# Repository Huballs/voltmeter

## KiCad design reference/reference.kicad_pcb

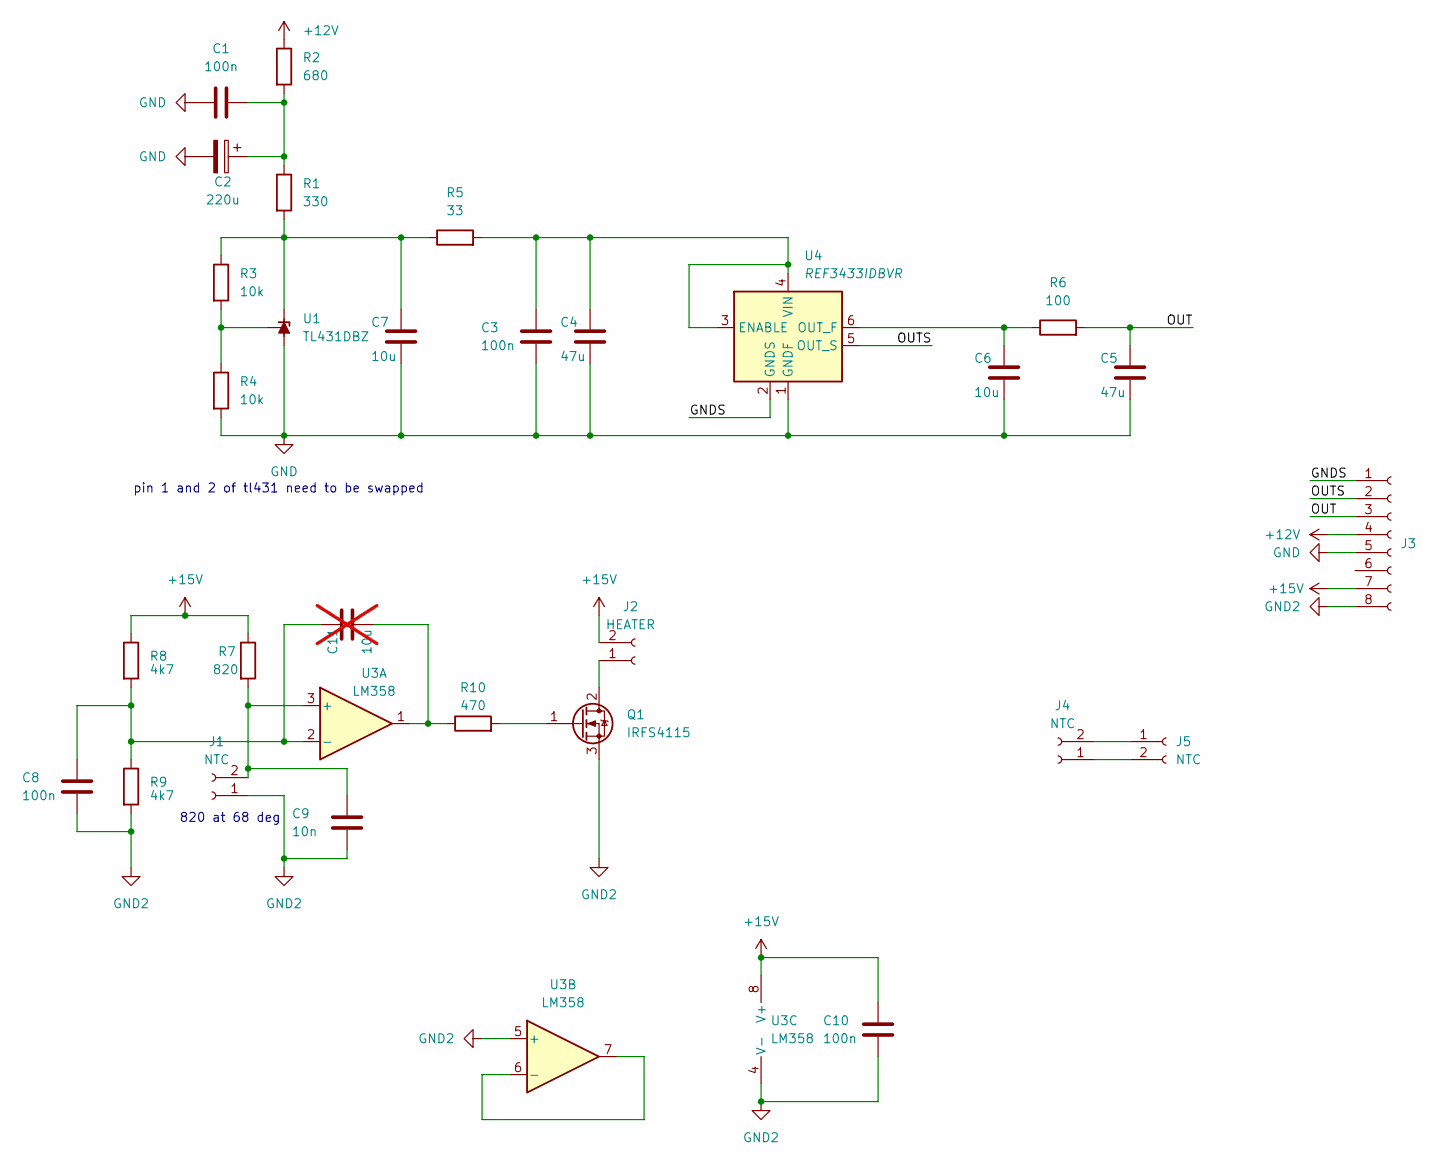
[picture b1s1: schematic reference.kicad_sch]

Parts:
C1, C3, C8, C10: 100n; C_0805_2012Metric_Pad1.18x1.45mm_HandSolder
C2: 220u; CP_EIA-7343-31_Kemet-D
C4, C5: 47u; C_0805_2012Metric_Pad1.18x1.45mm_HandSolder
C6, C7: 10u; C_0805_2012Metric_Pad1.18x1.45mm_HandSolder
C9: 10n; C_0805_2012Metric_Pad1.18x1.45mm_HandSolder
C11: 10u; C_0805_2012Metric_Pad1.18x1.45mm_HandSolder; not fitted
J1, J4, J5: NTC; PinHeader_1x02_P2.54mm_Vertical
J2: HEATER; PinHeader_1x02_P2.54mm_Vertical
J3: Conn_01x08_Socket; PinHeader_1x08_P2.54mm_Vertical
Q1: IRFS4115; TO-252-2
R1: 330; R_1206_3216Metric_Pad1.30x1.75mm_HandSolder
R2: 680; R_1206_3216Metric_Pad1.30x1.75mm_HandSolder
R3, R4: 10k; R_1206_3216Metric_Pad1.30x1.75mm_HandSolder
R5: 33; R_1206_3216Metric_Pad1.30x1.75mm_HandSolder
R6: 100; R_1206_3216Metric_Pad1.30x1.75mm_HandSolder
R7: 820; R_1206_3216Metric_Pad1.30x1.75mm_HandSolder
R8, R9: 4k7; R_1206_3216Metric_Pad1.30x1.75mm_HandSolder
R10: 470; R_1206_3216Metric_Pad1.30x1.75mm_HandSolder
U1: TL431DBZ; SOT-23
U3: LM358; SOIC-8_3.9x4.9mm_P1.27mm
U4: REF3433IDBVR; SOT-23-6

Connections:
+12V: J3.4, R2.1
+15V: C10.2, J2.2, J3.7, R7.1, R8.1, U3.8 (V+)
/GNDS: J3.1, U4.2 (GNDS)
/OUT: C5.2, J3.3, R6.2
/OUTS: J3.2, U4.5 (OUT_S)
GND: C1.1, C2.2, C3.1, C4.1, C5.1, C6.1, C7.1, J3.5, R4.2, U1.3 (A), U4.1 (GNDF)
GND2: C8.1, C9.1, C10.1, J1.1, J3.8, Q1.3 (S), R9.2, U3.4 (V-), U3.5 (+)
unnamed: C1.2, C2.1, R1.1, R2.2
unnamed: C11.1, R10.1, U3.1
unnamed: C9.2, J1.2, R7.2, U3.3 (+)
unnamed: J2.1, Q1.2 (D)
unnamed: J4.1, J5.2
unnamed: J4.2, J5.1
unnamed: Q1.1 (G), R10.2
unnamed: C7.2, R1.2, R3.1, R5.1, U1.1 (K)
unnamed: R3.2, R4.1, U1.2 (REF)
unnamed: C8.2, C11.2, R8.2, R9.1, U3.2 (-)
unnamed: U3.6 (-), U3.7
unnamed: C3.2, C4.2, R5.2, U4.3 (ENABLE), U4.4 (VIN)
unnamed: C6.2, R6.1, U4.6 (OUT_F)

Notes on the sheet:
pin 1 and 2 of tl431 need to be swapped
820 at 68 deg

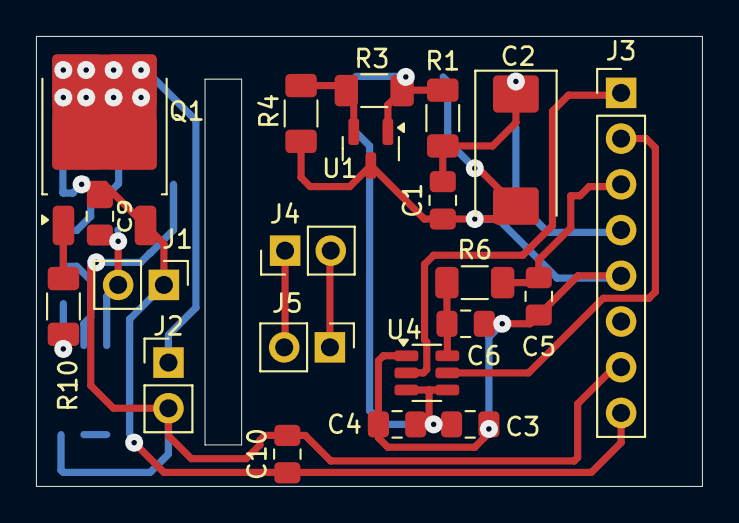
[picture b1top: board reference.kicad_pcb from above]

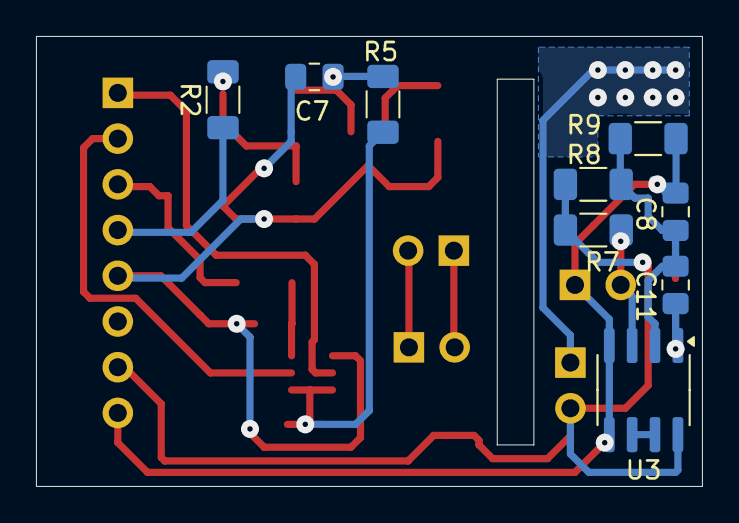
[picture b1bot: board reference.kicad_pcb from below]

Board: 2 copper layers, 37.0 x 25.0 mm, 30 parts (9 on the bottom side), 20 nets.

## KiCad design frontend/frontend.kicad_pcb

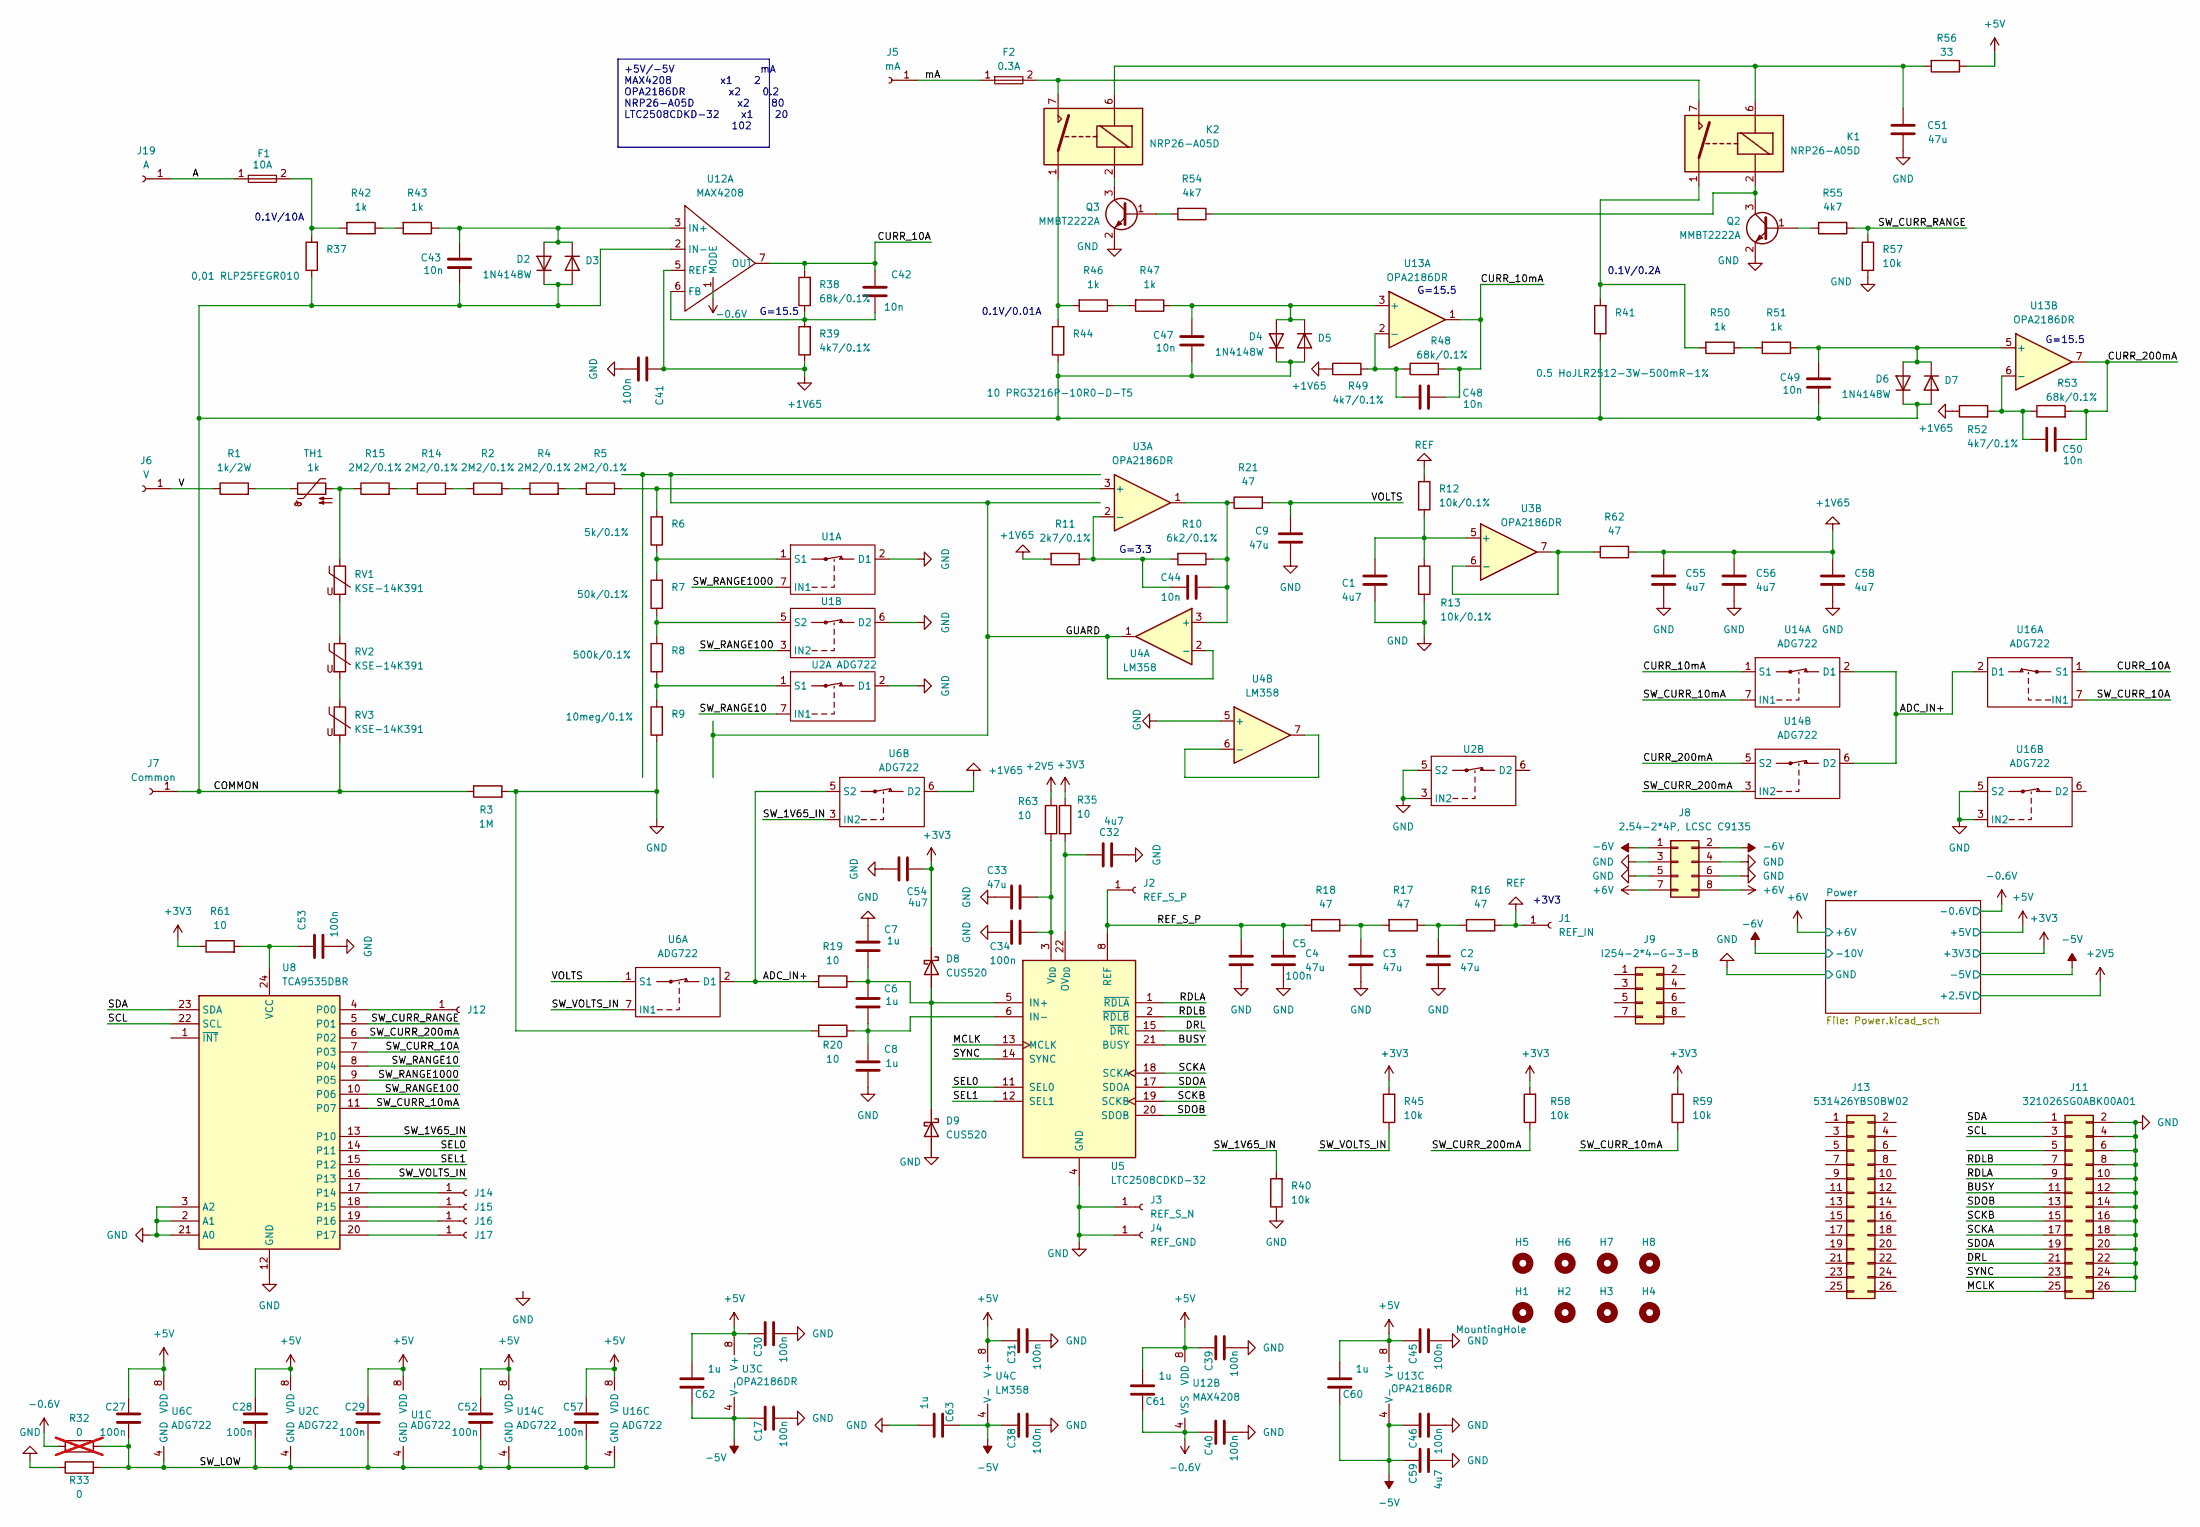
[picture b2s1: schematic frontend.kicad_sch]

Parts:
C1, C32, C54, C55, C56, C58, C59: 4u7; C_0805_2012Metric_Pad1.18x1.45mm_HandSolder
C2, C3, C4, C9, C33, C51: 47u; C_0805_2012Metric_Pad1.18x1.45mm_HandSolder
C5, C17, C27, C28, C29, C30, C31, C34, C38, C39, C40, C41, C45, C46, C52, C53, C57: 100n; C_0805_2012Metric_Pad1.18x1.45mm_HandSolder
C6, C7, C8, C60, C61, C62, C63: 1u; C_0805_2012Metric_Pad1.18x1.45mm_HandSolder
C42, C43, C44, C47, C48, C49, C50: 10n; C_0805_2012Metric_Pad1.18x1.45mm_HandSolder
D2, D3, D4, D5, D6, D7: 1N4148W; D_SOD-123
D8, D9: CUS520; D_SOD-323
F1: 10A; KLS5-266(FH-100)
F2: 0.3A; KLS5-266(FH-100)
H1, H2, H3, H4, H5, H6, H7, H8: MountingHole; MountingHole_3.2mm_M3
J1: REF_IN; PinHeader_1x01_P2.54mm_Vertical
J2: REF_S_P; PinHeader_1x01_P2.54mm_Vertical
J3: REF_S_N; PinHeader_1x01_P2.54mm_Vertical
J4: REF_GND; PinHeader_1x01_P2.54mm_Vertical
J5: mA; Conn-1-6x6-OD3mm
J6: V; Conn-1-6x6-OD3mm
J7: Common; Conn-1-6x6-OD3mm
J8: 2.54-2*4P, LCSC C9135; IDC-Header_2x04_P2.54mm_Vertical
J9: I254-2*4-G-3-B; IDC-Header_2x04_P2.54mm_Vertical
J11: 321026SG0ABK00A01; IDC-Header_2x13_P2.54mm_Vertical
J12, J14, J15, J16, J17: Conn_01x01_Socket; PinHeader_1x01_P2.54mm_Vertical
J13: 531426YBS0BW02; IDC-Header_2x13_P2.54mm_Vertical
J19: A; Conn-1-6x6-OD3mm
K1, K2: NRP26-A05D; NPR26
Q2, Q3: MMBT2222A; SOT-23
R1: 1k/2W; R_Axial_DIN0207_L6.3mm_D2.5mm_P15.24mm_Horizontal
R2, R4, R5, R14, R15: 2M2/0.1%; R_1206_3216Metric_Pad1.30x1.75mm_HandSolder
R3: 1M; R_1206_3216Metric_Pad1.30x1.75mm_HandSolder
R6: 5k/0.1%; R_1206_3216Metric_Pad1.30x1.75mm_HandSolder
R7: 50k/0.1%; R_1206_3216Metric_Pad1.30x1.75mm_HandSolder
R8: 500k/0.1%; R_1206_3216Metric_Pad1.30x1.75mm_HandSolder
R9: 10meg/0.1%; R_1206_3216Metric_Pad1.30x1.75mm_HandSolder
R10: 6k2/0.1%; R_1206_3216Metric_Pad1.30x1.75mm_HandSolder
R11: 2k7/0.1%; R_1206_3216Metric_Pad1.30x1.75mm_HandSolder
R12, R13: 10k/0.1%; R_1206_3216Metric_Pad1.30x1.75mm_HandSolder
R16, R17, R18, R21, R62: 47; R_1206_3216Metric_Pad1.30x1.75mm_HandSolder
R19, R20, R35, R61, R63: 10; R_1206_3216Metric_Pad1.30x1.75mm_HandSolder
R32: 0; R_1206_3216Metric_Pad1.30x1.75mm_HandSolder; not fitted
R33: 0; R_1206_3216Metric_Pad1.30x1.75mm_HandSolder
R37: 0,01 RLP25FEGR010; 2512 Big
R38, R48, R53: 68k/0.1%; R_1206_3216Metric_Pad1.30x1.75mm_HandSolder
R39, R49, R52: 4k7/0.1%; R_1206_3216Metric_Pad1.30x1.75mm_HandSolder
R40, R45, R57, R58, R59: 10k; R_1206_3216Metric_Pad1.30x1.75mm_HandSolder
R41: 0.5 HoJLR2512-3W-500mR-1%; R_2512_6332Metric
R42, R43, R46, R47, R50, R51: 1k; R_1206_3216Metric_Pad1.30x1.75mm_HandSolder
R44: 10 PRG3216P-10R0-D-T5; 1206 Vertical
R54, R55: 4k7; R_1206_3216Metric_Pad1.30x1.75mm_HandSolder
R56: 33; R_1206_3216Metric_Pad1.30x1.75mm_HandSolder
RV1, RV2, RV3: KSE-14K391; RV_Disc_D7mm_W3.7mm_P5mm
TH1: 1k; R_Axial_Power_L20.0mm_W6.4mm_P7.62mm_Vertical
U1, U2, U6, U14, U16: ADG722; uSOIC
U3, U13: OPA2186DR; VSSOP-8_3x3mm_P0.65mm
U4: LM358; SOIC-8_3.9x4.9mm_P1.27mm
U5: LTC2508CDKD-32; DFN-24-1EP_4x7mm_P0.5mm_EP2.64x6.44mm
U8: TCA9535DBR; SSOP-24_5.3x8.2mm_P0.65mm
U12: MAX4208; MSOP-8_3x3mm_P0.65mm

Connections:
+1V65: C41.1, C55.1, C56.1, C58.1, R11.2, R39.1, R49.1, R52.1, R62.2, U6.6 (D2), U12.5 (REF)
+2V5: R63.1; also elsewhere on the board
+3V3: C54.1, D8.1 (K), R35.1, R45.2, R58.2, R59.2, R61.1; also elsewhere on the board
+5V: C27.1, C28.1, C29.1, C30.1, C31.1, C39.1, C45.1, C52.1, C57.1, C60.2, C61.2, C62.2, R56.1, U1.8 (VDD), U2.8 (VDD), U3.8 (V+), U4.8 (V+), U6.8 (VDD), U12.8 (VDD), U13.8 (V+), U14.8 (VDD), U16.8 (VDD); also elsewhere on the board
+6V: J8.7, J8.8; also elsewhere on the board
-0.6V: C40.1, C61.1, R32.1, U12.1 (MODE), U12.4 (VSS); also elsewhere on the board
-5V: C17.1, C38.1, C46.1, C59.1, C60.1, C62.1, C63.1, U3.4 (V-), U4.4 (V-), U13.4 (V-); also elsewhere on the board
-6V: J8.1, J8.2; also elsewhere on the board
/A: F1.1, J19.1
/ADC_IN+: R19.2, U6.2 (D1), U6.5 (S2), U14.2 (D1), U14.6 (D2), U16.2 (D1)
/BUSY: J11.11, U5.21 (BUSY)
/COMMON: C43.2, C47.2, C49.2, D2.1 (K), D3.2 (A), D4.1 (K), D5.2 (A), D6.1 (K), D7.2 (A), J7.1, R3.1, R37.1, R41.1, R44.1, RV3.2, U12.2 (IN-)
/CURR_10A: C42.1, R38.2, U12.7 (OUT), U16.1 (S1)
/CURR_10mA: C48.2, R48.2, U13.1, U14.1 (S1)
/CURR_200mA: C50.2, R53.2, U13.7, U14.5 (S2)
/DRL: J11.21, U5.15 (~DRL)
/GUARD: U4.1, U4.2 (-)
/MCLK: J11.25, U5.13 (MCLK)
/RDLA: J11.9, U5.1 (~RDLA)
/RDLB: J11.7, U5.2 (~RDLB)
/REF_S_P: C4.1, C5.1, J2.1, R18.2, U5.8 (REF), U5.9 (REF), U5.10 (REF)
/SCKA: J11.17, U5.18 (SCKA)
/SCKB: J11.15, U5.19 (SCKB)
/SCL: J11.3, U8.22 (SCL)
/SDA: J11.1, U8.23 (SDA)
/SDOA: J11.19, U5.17 (SDOA)
/SDOB: J11.13, U5.20 (SDOB)
/SEL0: U5.11 (SEL0), U8.14 (P11)
/SEL1: U5.12 (SEL1), U8.15 (P12)
/SW_1V65_IN: R40.2, U6.3 (IN2), U8.13 (P10)
/SW_CURR_10A: U8.7 (P03), U16.7 (IN1)
/SW_CURR_10mA: R59.1, U8.11 (P07), U14.7 (IN1)
/SW_CURR_200mA: R58.1, U8.6 (P02), U14.3 (IN2)
/SW_CURR_RANGE: R55.1, R57.1, U8.5 (P01)
/SW_LOW: C27.2, C28.2, C29.2, C52.2, C57.2, R32.2, R33.2, U1.4 (GND), U2.4 (GND), U6.4 (GND), U14.4 (GND), U16.4 (GND)
/SW_RANGE10: U2.7 (IN1), U8.8 (P04)
/SW_RANGE100: U1.3 (IN2), U8.10 (P06)
/SW_RANGE1000: U1.7 (IN1), U8.9 (P05)
/SW_VOLTS_IN: R45.1, U6.7 (IN1), U8.16 (P13)
/SYNC: J11.23, U5.14 (SYNC)
/V: J6.1, R1.1
/VOLTS: C9.1, R21.2, U6.1 (S1)
/mA: F2.1, J5.1
GND: C1.2, C2.2, C3.2, C4.2, C5.2, C7.1, C8.2, C9.2, C17.2, C30.2, C31.2, C32.2, C33.2, C34.2, C38.2, C39.2, C40.2, C41.2, C45.2, C46.2, C51.2, C53.2, C54.2, C55.2, C56.2, C58.2, C59.2, C63.2, D9.2 (A), J3.1, J4.1, J8.3, J8.4, J8.5, J8.6, J11.2, J11.4, J11.6, J11.8, J11.10, J11.12, J11.14, J11.16, J11.18, J11.20, J11.22, J11.24, J11.26, Q2.2 (E), Q3.2 (E), R3.2, R9.1, R13.2, R20.2, R33.1, R40.1, R57.2, U1.2 (D1), U1.6 (D2), U2.2 (D1), U2.3 (IN2), U2.5 (S2), U4.5 (+), U5.4 (GND), U5.7 (GND), U5.16 (GND), U5.23 (GND), U5.24 (GND), U5.25 (GND), U8.2 (A1), U8.3 (A2), U8.12 (GND), U8.21 (A0), U16.3 (IN2), U16.5 (S2); also elsewhere on the board
unnamed: C2.1, R16.2, R17.1
unnamed: C3.1, R17.2, R18.1
unnamed: C51.1, K1.6, K2.6, R56.2
unnamed: C43.1, D2.2 (A), D3.1 (K), R43.1, U12.3 (IN+)
unnamed: C47.1, D4.2 (A), D5.1 (K), R47.1, U13.3 (+)
unnamed: C49.1, D6.2 (A), D7.1 (K), R51.1, U13.5 (+)
unnamed: C6.1, C7.2, D8.2 (A), D9.1 (K), R19.1, U5.5 (IN+)
unnamed: F1.2, R37.2, R42.2
unnamed: F2.2, K1.7, K1.8, K2.7, K2.8
unnamed: J12.1, U8.4 (P00)
unnamed: J14.1, U8.17 (P14)
unnamed: J15.1, U8.18 (P15)
unnamed: J16.1, U8.19 (P16)
unnamed: J17.1, U8.20 (P17)
unnamed: K1.1, K1.14, R41.2, R50.2
unnamed: K2.1, K2.14, R44.2, R46.2
unnamed: Q2.1 (B), R55.2
unnamed: K1.2, Q2.3 (C), R54.1
unnamed: Q3.1 (B), R54.2
unnamed: K2.2, Q3.3 (C)
unnamed: R1.2, TH1.1
unnamed: R2.2, R4.1
unnamed: R4.2, R5.1
unnamed: R14.1, R15.2
unnamed: R2.1, R14.2
unnamed: R15.1, RV1.1, TH1.2
unnamed: R42.1, R43.2
unnamed: R46.1, R47.2
unnamed: R50.1, R51.2
unnamed: RV1.2, RV2.1
unnamed: RV2.2, RV3.1
unnamed: R6.1, R7.2, U1.1 (S1)
unnamed: R7.1, R8.2, U1.5 (S2)
unnamed: R8.1, R9.2, U2.1 (S1)
unnamed: R5.2, R6.2, U3.3 (+)
unnamed: C44.1, R10.2, R11.1, U3.2 (-)
unnamed: C1.1, R12.2, R13.1, U3.5 (+)
unnamed: R62.1, U3.6 (-), U3.7
unnamed: C44.2, R10.1, R21.1, U3.1, U4.3 (+)
unnamed: U4.6 (-), U4.7
unnamed: C6.2, C8.1, R20.1, U5.6 (IN-)
unnamed: C32.1, R35.2, U5.22 (OV_{DD})
unnamed: C33.1, C34.1, R63.2, U5.3 (V_{DD})
unnamed: C53.1, R61.2, U8.24 (VCC)
unnamed: C42.2, R38.1, R39.2, U12.6 (FB)
unnamed: C48.1, R48.1, R49.2, U13.2 (-)
unnamed: C50.1, R52.2, R53.1, U13.6 (-)
REF: J1.1, R12.1, R16.1

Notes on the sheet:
+5V/-5V mA MAX4208 x1 2 OPA2186DR x2 0.2 NRP26-A05D x2 80 LTC2508CDKD-32 x1 20 102
+3V3
G=15.5
G=3.3
0.1V/10A
0.1V/0.01A
0.1V/0.2A

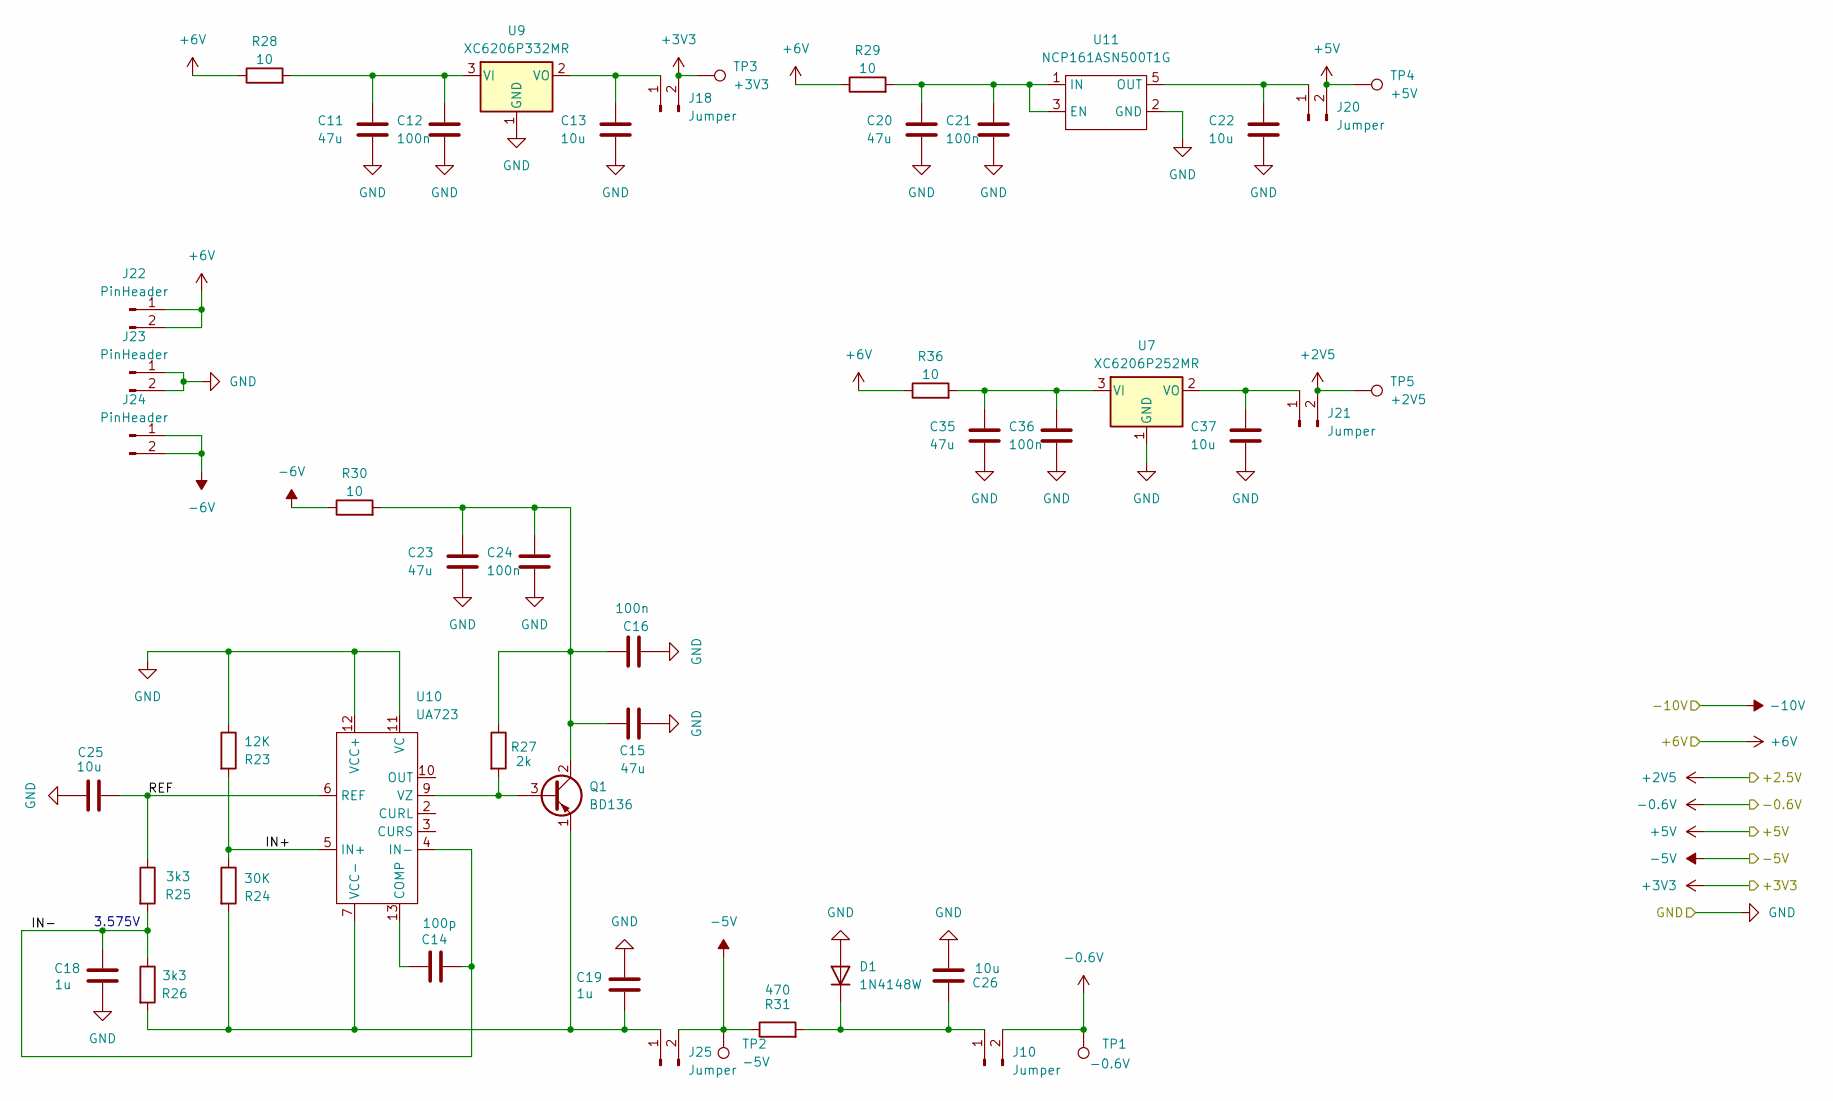
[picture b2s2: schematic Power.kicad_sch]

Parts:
C11, C15, C20, C23, C35: 47u; C_0805_2012Metric_Pad1.18x1.45mm_HandSolder
C12, C16, C21, C24, C36: 100n; C_0805_2012Metric_Pad1.18x1.45mm_HandSolder
C13, C22, C25, C26, C37: 10u; C_0805_2012Metric_Pad1.18x1.45mm_HandSolder
C14: 100p; C_0805_2012Metric_Pad1.18x1.45mm_HandSolder
C18, C19: 1u; C_0805_2012Metric_Pad1.18x1.45mm_HandSolder
D1: 1N4148W; D_SOD-123
J10, J18, J20, J21, J25: Jumper; PinHeader_1x02_P2.54mm_Vertical
J22, J23, J24: PinHeader; PinHeader_1x02_P2.54mm_Vertical
Q1: BD136; TO-126-3_Vertical
R23: 12K; R_1206_3216Metric_Pad1.30x1.75mm_HandSolder
R24: 30K; R_1206_3216Metric_Pad1.30x1.75mm_HandSolder
R25, R26: 3k3; R_1206_3216Metric_Pad1.30x1.75mm_HandSolder
R27: 2k; R_1206_3216Metric_Pad1.30x1.75mm_HandSolder
R28, R29, R30, R36: 10; R_1206_3216Metric_Pad1.30x1.75mm_HandSolder
R31: 470; R_1206_3216Metric_Pad1.30x1.75mm_HandSolder
TP1: -0.6V; Pin_D1.3mm_L11.3mm_W2.8mm_Flat
TP2: -5V; Pin_D1.3mm_L11.3mm_W2.8mm_Flat
TP3: +3V3; Pin_D1.3mm_L11.3mm_W2.8mm_Flat
TP4: +5V; Pin_D1.3mm_L11.3mm_W2.8mm_Flat
TP5: +2V5; Pin_D1.3mm_L11.3mm_W2.8mm_Flat
U7: XC6206P252MR; SOT-23-3
U9: XC6206P332MR; SOT-23-3
U10: UA723; SO-14_3.9x8.65mm_P1.27mm
U11: NCP161ASN500T1G; SOT-23-5_HandSoldering

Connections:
+2V5: J21.2, TP5.1; also elsewhere on the board
+3V3: J18.2, TP3.1; also elsewhere on the board
+5V: J20.2, TP4.1; also elsewhere on the board
+6V: J22.1, J22.2, R28.1, R29.1, R36.1; also elsewhere on the board
-0.6V: J10.2, TP1.1; also elsewhere on the board
-5V: J25.2, R31.1, TP2.1; also elsewhere on the board
-6V: J24.1, J24.2, R30.1; also elsewhere on the board
/Power/IN+: R23.2, R24.1, U10.5 (IN+)
/Power/IN-: C14.2, C18.2, R25.2, R26.1, U10.4 (IN-)
/Power/REF: C25.2, R25.1, U10.6 (REF)
GND: C11.2, C12.2, C13.2, C15.2, C16.2, C18.1, C19.2, C20.2, C21.2, C22.2, C23.2, C24.2, C25.1, C26.2, C35.2, C36.2, C37.2, D1.2 (A), J23.1, J23.2, R23.1, U7.1 (GND), U9.1 (GND), U10.11 (VC), U10.12 (VCC+), U11.2 (GND); also elsewhere on the board
unnamed: C26.1, D1.1 (K), J10.1, R31.2
unnamed: C13.1, J18.1, U9.2 (VO)
unnamed: C22.1, J20.1, U11.5 (OUT)
unnamed: C37.1, J21.1, U7.2 (VO)
unnamed: C19.1, J25.1, Q1.1 (E), R24.2, R26.2, U10.7 (VCC-)
unnamed: Q1.3 (B), R27.2, U10.9 (VZ)
unnamed: C15.1, C16.1, C23.1, C24.1, Q1.2 (C), R27.1, R30.2
unnamed: C35.1, C36.1, R36.2, U7.3 (VI)
unnamed: C11.1, C12.1, R28.2, U9.3 (VI)
unnamed: C14.1, U10.13 (COMP)
unnamed: C20.1, C21.1, R29.2, U11.1 (IN), U11.3 (EN)

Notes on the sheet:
3.575V

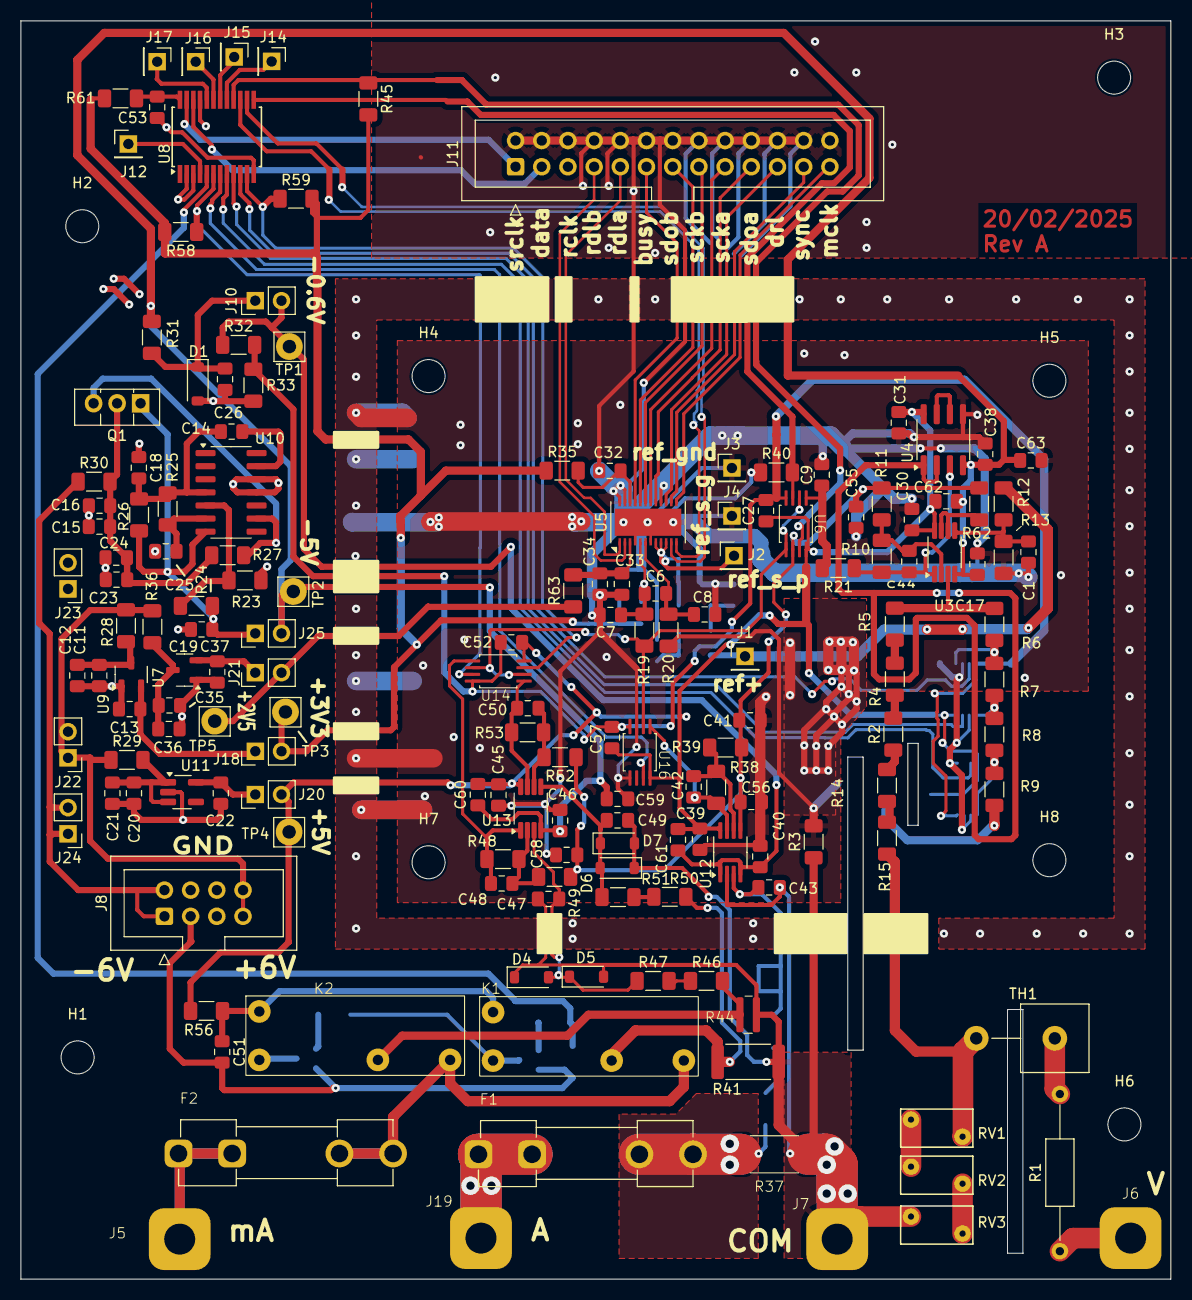
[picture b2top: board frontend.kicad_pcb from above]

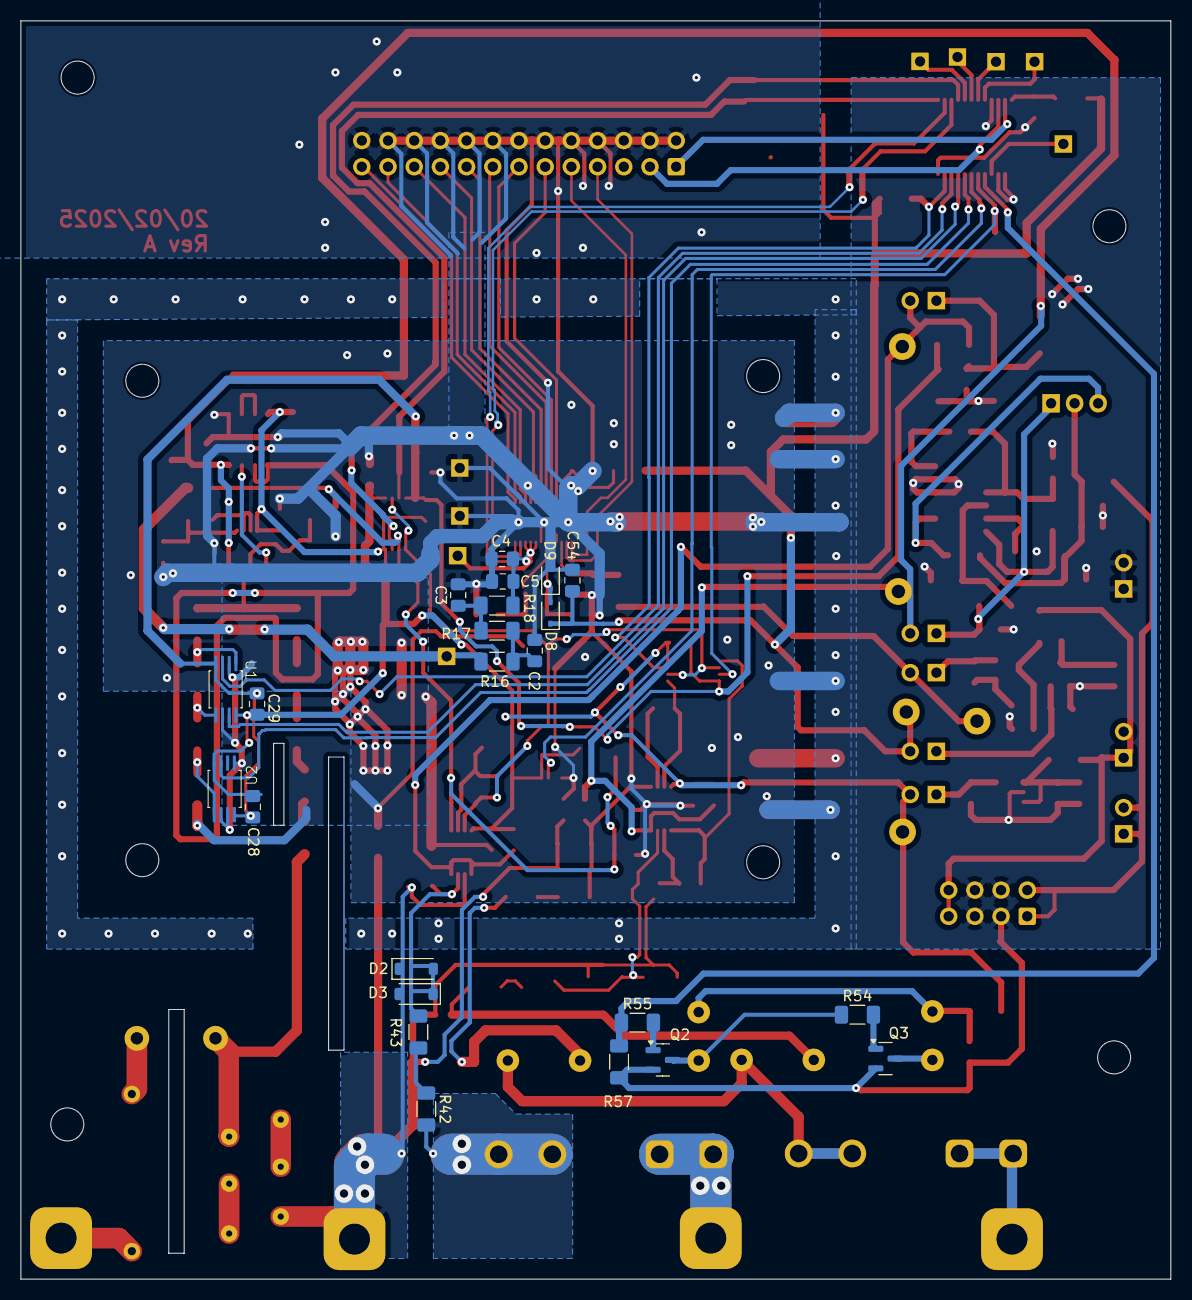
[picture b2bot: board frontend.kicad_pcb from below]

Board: 2 copper layers, 111.5 x 122.0 mm, 193 parts (23 on the bottom side), 106 nets.

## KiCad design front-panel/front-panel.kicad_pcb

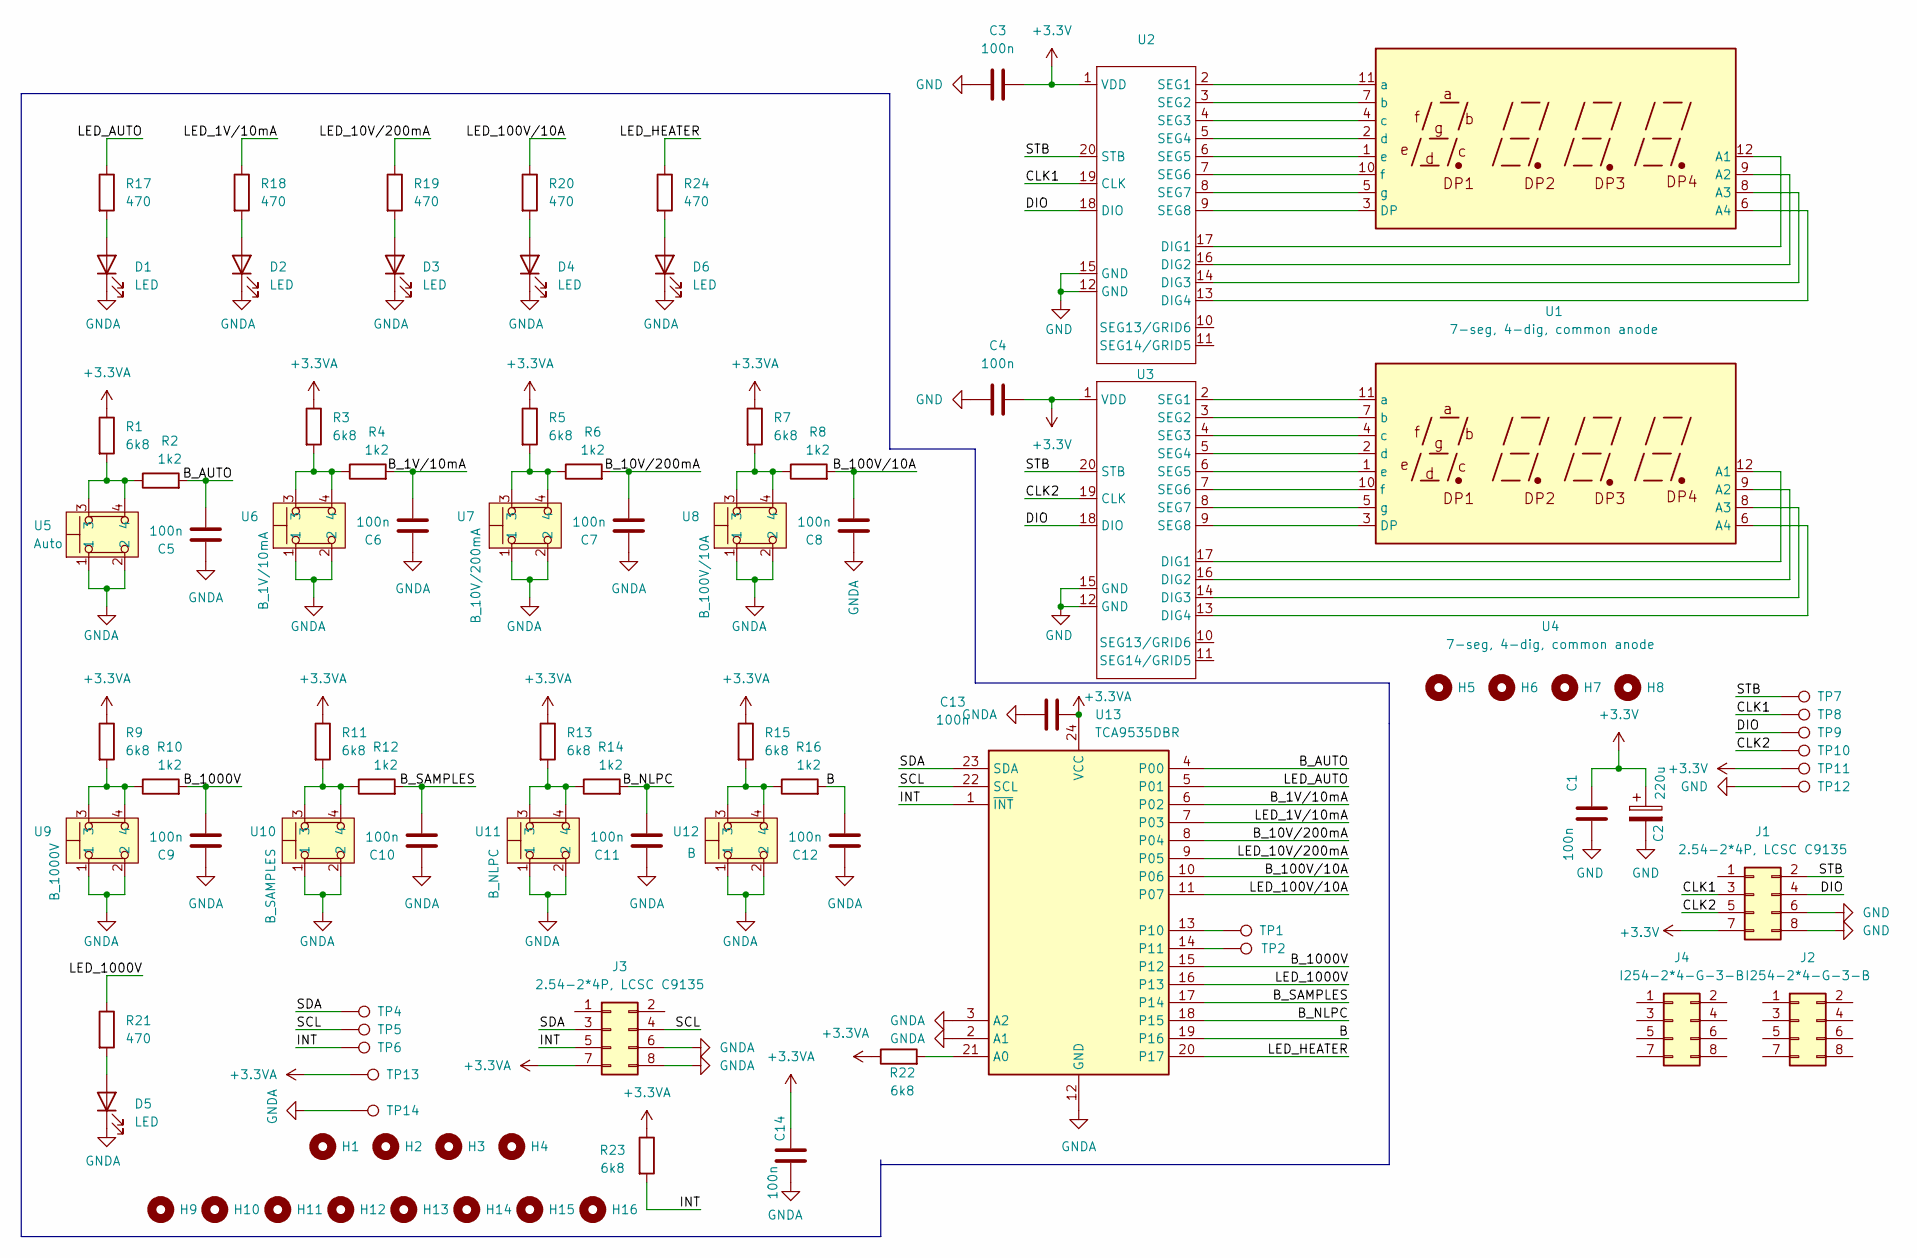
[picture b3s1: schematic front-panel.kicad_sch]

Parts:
C1, C3, C4, C5, C6, C7, C8, C9, C10, C11, C12, C13, C14: 100n; C_0805_2012Metric_Pad1.18x1.45mm_HandSolder
C2: 220u; CP_EIA-7343-31_Kemet-D
D1, D2, D3, D4, D5, D6: LED; led_3mm_mid_hole
H1, H2, H3, H4, H5, H6, H7, H8: MountingHole; MountingHole_3.2mm_M3
H9, H10, H11, H12, H13, H14, H15, H16: MountingHole; Hole_3mm
J1, J3: 2.54-2*4P, LCSC C9135; IDC-Header_2x04_P2.54mm_Vertical
J2, J4: I254-2*4-G-3-B; IDC-Header_2x04_P2.54mm_Vertical
R1, R3, R5, R7, R9, R11, R13, R15, R22, R23: 6k8; R_1206_3216Metric_Pad1.30x1.75mm_HandSolder
R2, R4, R6, R8, R10, R12, R14, R16: 1k2; R_1206_3216Metric_Pad1.30x1.75mm_HandSolder
R17, R18, R19, R20, R21, R24: 470; R_1206_3216Metric_Pad1.30x1.75mm_HandSolder
TP1, TP2, TP4, TP5, TP6, TP7, TP8, TP9, TP10, TP11, TP12, TP13, TP14: TestPoint; Pin_D0.9mm_L10.0mm_W2.4mm_FlatFork
U1, U4: 7-seg, 4-dig, common anode; 7_segment,_4_dig,_0.4_inch_anode
U2, U3: SSOP-20_4.4x6.5mm_P0.65mm
U5: Auto; Tact_Button_SMD_Gold
U6: B_1V/10mA; Tact_Button_SMD_Gold
U7: B_10V/200mA; Tact_Button_SMD_Gold
U8: B_100V/10A; Tact_Button_SMD_Gold
U9: B_1000V; Tact_Button_SMD_Gold
U10: B_SAMPLES; Tact_Button_SMD_Gold
U11: B_NLPC; Tact_Button_SMD_Gold
U12: B; Tact_Button_SMD_Gold
U13: TCA9535DBR; SSOP-24_5.3x8.2mm_P0.65mm

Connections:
+3.3V: C1.2, C2.1, C3.2, C4.2, J1.7, TP11.1, U2.1 (VDD), U3.1 (VDD)
+3.3VA: C13.2, C14.2, J3.7, R1.1, R3.1, R5.1, R7.1, R9.1, R11.1, R13.1, R15.1, R22.1, R23.1, TP13.1, U13.24 (VCC)
/B: C12.2, R16.2, U13.19 (P16)
/B_1V/10mA: C6.2, R4.2, U13.6 (P02)
/B_10V/200mA: C7.2, R6.2, U13.8 (P04)
/B_100V/10A: C8.2, R8.2, U13.10 (P06)
/B_1000V: C9.2, R10.2, U13.15 (P12)
/B_AUTO: C5.2, R2.2, U13.4 (P00)
/B_NLPC: C11.2, R14.2, U13.18 (P15)
/B_SAMPLES: C10.2, R12.2, U13.17 (P14)
/CLK1: J1.3, TP8.1, U2.19 (CLK)
/CLK2: J1.5, TP10.1, U3.19 (CLK)
/DIO: J1.4, TP9.1, U2.18 (DIO), U3.18 (DIO)
/INT: J3.5, R23.2, TP6.1, U13.1 (~INT)
/LED_1V/10mA: R18.1, U13.7 (P03)
/LED_10V/200mA: R19.1, U13.9 (P05)
/LED_100V/10A: R20.1, U13.11 (P07)
/LED_1000V: R21.1, U13.16 (P13)
/LED_AUTO: R17.1, U13.5 (P01)
/LED_HEATER: R24.1, U13.20 (P17)
/SCL: J3.4, TP5.1, U13.22 (SCL)
/SDA: J3.3, TP4.1, U13.23 (SDA)
/STB: J1.2, TP7.1, U2.20 (STB), U3.20 (STB)
GND: C1.1, C2.2, C3.1, C4.1, J1.6, J1.8, TP12.1, U2.12 (GND), U2.15 (GND), U3.12 (GND), U3.15 (GND)
GNDA: C5.1, C6.1, C7.1, C8.1, C9.1, C10.1, C11.1, C12.1, C13.1, C14.1, D1.1 (K), D2.1 (K), D3.1 (K), D4.1 (K), D5.1 (K), D6.1 (K), J3.6, J3.8, TP14.1, U5.1, U5.2, U6.1, U6.2, U7.1, U7.2, U8.1, U8.2, U9.1, U9.2, U10.1, U10.2, U11.1, U11.2, U12.1, U12.2, U13.2 (A1), U13.3 (A2), U13.12 (GND)
unnamed: D1.2 (A), R17.2
unnamed: D2.2 (A), R18.2
unnamed: D3.2 (A), R19.2
unnamed: D4.2 (A), R20.2
unnamed: D5.2 (A), R21.2
unnamed: D6.2 (A), R24.2
unnamed: R1.2, R2.1, U5.3, U5.4
unnamed: R3.2, R4.1, U6.3, U6.4
unnamed: R5.2, R6.1, U7.3, U7.4
unnamed: R7.2, R8.1, U8.3, U8.4
unnamed: R9.2, R10.1, U9.3, U9.4
unnamed: R11.2, R12.1, U10.3, U10.4
unnamed: R13.2, R14.1, U11.3, U11.4
unnamed: R15.2, R16.1, U12.3, U12.4
unnamed: U1.12 (A1), U2.17 (DIG1)
unnamed: U1.9 (A2), U2.16 (DIG2)
unnamed: U1.8 (A3), U2.14 (DIG3)
unnamed: U1.6 (A4), U2.13 (DIG4)
unnamed: U1.3 (DP), U2.9 (SEG8)
unnamed: U1.11 (a), U2.2 (SEG1)
unnamed: U1.7 (b), U2.3 (SEG2)
unnamed: U1.4 (c), U2.4 (SEG3)
unnamed: U1.2 (d), U2.5 (SEG4)
unnamed: U1.1 (e), U2.6 (SEG5)
unnamed: U1.10 (f), U2.7 (SEG6)
unnamed: U1.5 (g), U2.8 (SEG7)
unnamed: U3.17 (DIG1), U4.12 (A1)
unnamed: U3.16 (DIG2), U4.9 (A2)
unnamed: U3.14 (DIG3), U4.8 (A3)
unnamed: U3.13 (DIG4), U4.6 (A4)
unnamed: U3.2 (SEG1), U4.11 (a)
unnamed: U3.3 (SEG2), U4.7 (b)
unnamed: U3.4 (SEG3), U4.4 (c)
unnamed: U3.5 (SEG4), U4.2 (d)
unnamed: U3.6 (SEG5), U4.1 (e)
unnamed: U3.7 (SEG6), U4.10 (f)
unnamed: U3.8 (SEG7), U4.5 (g)
unnamed: U3.9 (SEG8), U4.3 (DP)
unnamed: R22.2, U13.21 (A0)
unnamed: TP1.1, U13.13 (P10)
unnamed: TP2.1, U13.14 (P11)
